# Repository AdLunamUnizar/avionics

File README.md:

# avionics
Repositorio del departamento de electrónica del equipo de cohetería ALUnizar.

Como microcontrolador se está usando una placa [Arduino Nano](https://docs.arduino.cc/hardware/nano/)

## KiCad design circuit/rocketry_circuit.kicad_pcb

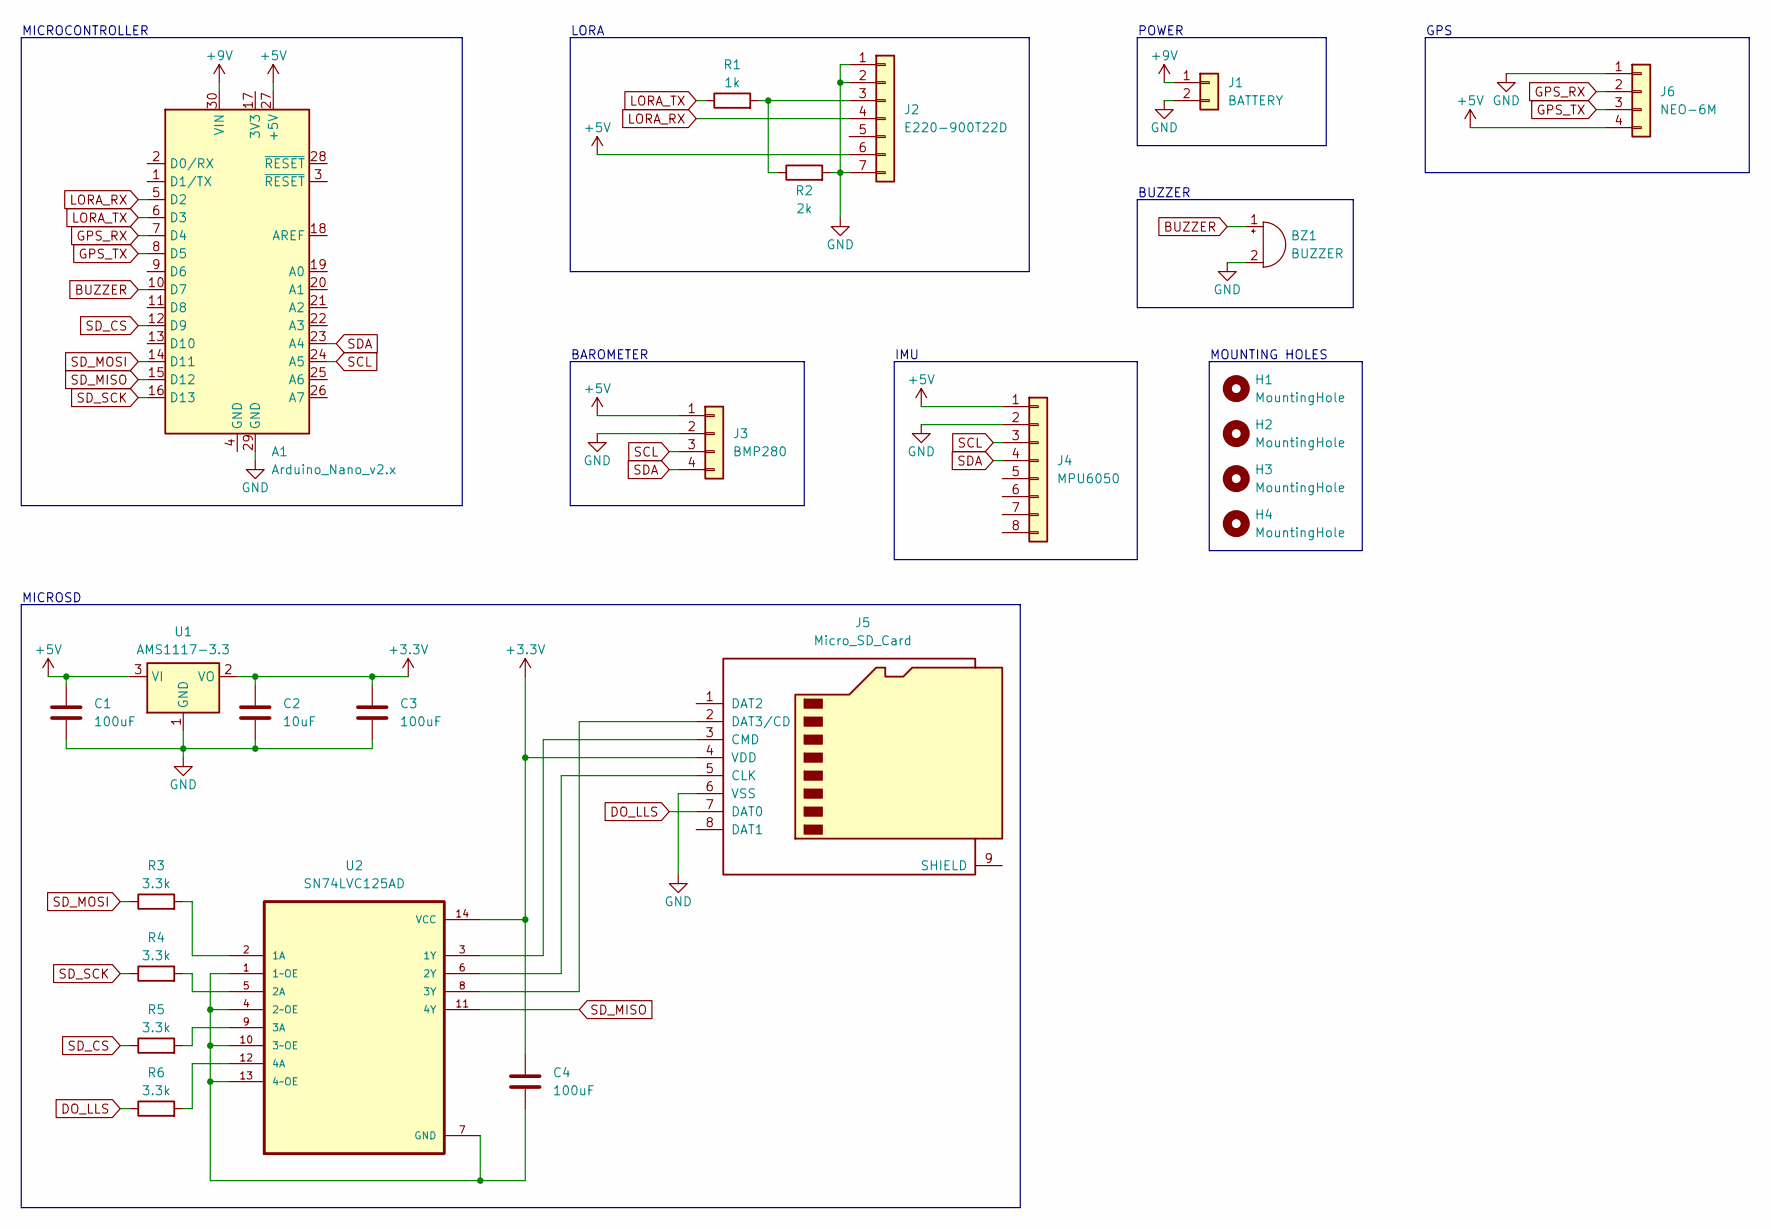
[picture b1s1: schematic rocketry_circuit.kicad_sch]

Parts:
A1: Arduino_Nano_v2.x; Arduino_Nano
BZ1: BUZZER; Buzzer_12x9.5RM7.6
C1, C3: 100uF; C_0603_1608Metric
C2: 10uF; C_0603_1608Metric
C4: 100uF; C_0805_2012Metric
H1, H2, H3, H4: MountingHole; MountingHole_3.2mm_M3_ISO7380
J1: BATTERY; PinHeader_1x02_P2.54mm_Vertical
J2: E220-900T22D; PinHeader_1x07_P2.54mm_Vertical
J3: BMP280; PinHeader_1x04_P2.54mm_Vertical
J4: MPU6050; PinHeader_1x08_P2.54mm_Vertical
J5: Micro_SD_Card; J_SD_Card-micro_socket_A
J6: NEO-6M; PinHeader_1x04_P2.54mm_Vertical
R1: 1k; R_Axial_DIN0204_L3.6mm_D1.6mm_P5.08mm_Horizontal
R2: 2k; R_Axial_DIN0204_L3.6mm_D1.6mm_P5.08mm_Horizontal
R3, R4, R5, R6: 3.3k; R_0603_1608Metric
U1: AMS1117-3.3; SOT-223-3_TabPin2
U2: SN74LVC125AD; TSSOP

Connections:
+3.3V: C2.1, C3.1, C4.1, J5.4 (VDD), U1.2 (VO), U2.14 (VCC)
+5V: A1.27 (+5V), C1.1, J2.6, J3.1, J4.1, J6.4, U1.3 (VI)
+9V: A1.30 (VIN), J1.1
BUZZER: A1.10 (D7), BZ1.1 (-)
DO_LLS: J5.7 (DAT0), R6.1
GND: A1.29 (GND), BZ1.2 (+), C1.2, C2.2, C3.2, J1.2, J2.1, J2.2, J2.7, J3.2, J4.2, J5.6 (VSS), J6.1, R2.2, U1.1 (GND)
GPS_RX: A1.7 (D4), J6.2
GPS_TX: A1.8 (D5), J6.3
LORA_RX: A1.5 (D2), J2.4
LORA_TX: A1.6 (D3), R1.1
unnamed: J2.3, R1.2, R2.1
unnamed: J5.5 (CLK), U2.6 (2Y)
unnamed: J5.3 (CMD), U2.3 (1Y)
unnamed: J5.2 (DAT3/CD), U2.8 (3Y)
unnamed: R3.2, U2.2 (1A)
unnamed: C4.2, U2.1 (1~OE), U2.4 (2~OE), U2.7 (GND), U2.10 (3~OE), U2.13 (4~OE)
unnamed: R4.2, U2.5 (2A)
unnamed: R5.2, U2.9 (3A)
unnamed: R6.2, U2.12 (4A)
SCL: A1.24 (A5), J3.3, J4.3
SDA: A1.23 (A4), J3.4, J4.4
SD_CS: A1.12 (D9), R5.1
SD_MISO: A1.15 (D12), U2.11 (4Y)
SD_MOSI: A1.14 (D11), R3.1
SD_SCK: A1.16 (D13), R4.1

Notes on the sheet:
POWER
BUZZER
BAROMETER
GPS
IMU
MICROSD
MICROCONTROLLER
MOUNTING HOLES
LORA

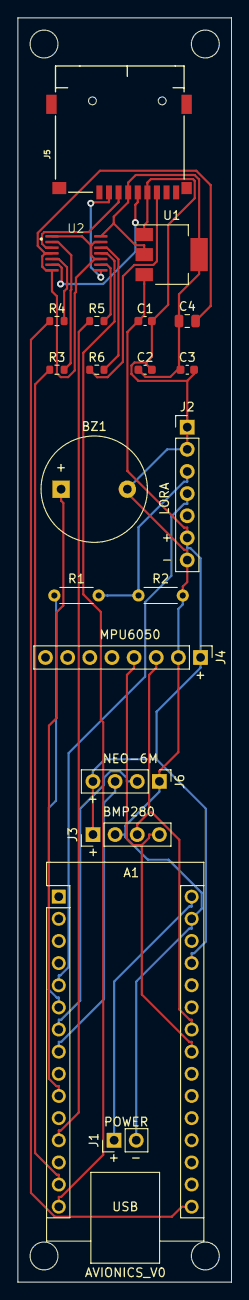
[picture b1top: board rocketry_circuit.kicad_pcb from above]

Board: 2 copper layers, 24.5 x 145.0 mm, 24 parts (0 on the bottom side), 25 nets.

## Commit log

2023-06-17 cansats code
2023-06-20 main
2023-06-30 Cambio algoritmo a detectar apogeo con medidas barométricas
2023-06-30 Cambio en comentarios y solucionar naming
2023-06-30 serial altitude
2023-07-02 Permite recibir un comando por puerto serie para calibrar barómetro
2023-07-02 Actualización condición detectar despegue
2023-09-07 circuit
2023-09-07 resistor between gate and source
2023-09-19 LORA serial, calibrate baro, HIGH buzzer and parachute
2023-09-21 telemetry + timer 11 sec (+3sec delay)
2023-09-21 Baro y timer independientes
2023-09-22 Version NO FINAL
2024-01-30 rocketry circuit
2024-02-06 sddfsdfd
2024-02-06 ougn
    lubug
2024-02-12 esquemas
    gps y sensor de presión
2024-02-12 schematics
2024-03-30 Footprint for microsd
2024-04-09 Footprint for resistors R1 R2
